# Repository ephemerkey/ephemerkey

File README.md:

# ephemerkey

A battery-powered, **GPS-geofenced TOTP code generator**. It produces RFC 6238
time-based one-time passwords (TOTP) — but only when the device holds a valid
GNSS fix inside an authorized geofence. Outside the fence, no codes. A companion
analog "TOTP lock" board consumes the codes and drives an actuator.

> Time comes from GNSS (disciplined RTC), place comes from GNSS — so a code is
> proof of *being in the right place at the right time*.

## Features

- **GNSS time + place**: u-blox MAX-M10S provides UTC time (TIMEPULSE-disciplined
  RTC) and a position fix. Codes are gated on both an accurate clock and a fix
  inside the configured geofence.
- **RFC 6238 TOTP**: SHA1/HMAC/Base32 engine from the `smalltotp` library,
  6-digit / 30-second codes (configurable).
- **Ultra-low-power**: STM32U083 (Cortex-M0+ ULP) + TPS63900 buck-boost with
  nanoamp-class quiescent current for long battery life; GNSS duty-cycled.
- **Tamper / motion**: LIS3DH accelerometer for wake-on-motion and tamper
  detection (optionally zeroizes the secret on tamper).
- **Single coin/Li-ion cell** input via buck-boost (works above and below 3.3 V).

## Architecture

```
                    ┌───────────────── RF ─────────────────┐
   W3011A chip ANT ─┤  (50Ω + π-match)                      │
                    └──────────────┬───────────────────────┘
                                   │ RF_IN
                          ┌────────┴─────────┐
                          │  MAX-M10S-00B    │  u-blox M10 GNSS
                          │  (TCXO, LNA, SAW)│
                          └─┬───┬────┬───┬───┘
                   UART(TXD/RXD)│    │TIMEPULSE (1 PPS → RTC discipline)
                            │   │EXTINT (wake)
                            │   │
   batt ── TPS63900 ──3V3───┼───┴──────────────┐
   (buck-boost,             │                  │
    ultra-low Iq)           │ USART1           │ V_BCKP (RTC/GNSS backup)
                     ┌───────┴────────┐         │
                     │  STM32U083KCU6 │         │
                     │  Cortex-M0+    │── RTC ──┘ (TOTP time base)
                     │  256KB flash   │
                     └─┬────┬────┬────┘
                  I2C  │    │    │ SWD (PA13/PA14)
                  ┌────┴──┐ │    │
                  │LIS3DH │ │    └── USB (PA11/PA12) — provisioning/console
                  │ accel │ │
                  └───────┘ └── code out → companion "TOTP lock" board
                  (motion/tamper)   (UART / open-drain / display)
```

## Repository Structure

```
ephemerkey/
├── hardware/                    # PCB design (KiCad 10, CERN-OHL-P v2)
│   ├── lib/                     # empty — anchor parts use KiCad bundled libs
│   │   ├── symbols/             #   (reserved for future custom symbols)
│   │   ├── footprints.pretty/   #   (reserved for future custom footprints)
│   │   └── 3dmodels/            #   (reserved for future 3D STEP models)
│   ├── ephemerkey/              # The generator board
│   │   ├── ephemerkey.kicad_pro
│   │   ├── ephemerkey.kicad_sch # Top-level: MCU, USB, SWD, button, LED
│   │   ├── psu.kicad_sch        # Battery → TPS63900 buck-boost sub-sheet
│   │   ├── gnss.kicad_sch       # MAX-M10S + W3011A antenna sub-sheet
│   │   └── sensors.kicad_sch    # LIS3DH accelerometer sub-sheet
│   ├── scripts/
│   ├── Makefile
│   ├── sym-lib-table
│   └── fp-lib-table
├── firmware/
│   ├── ephemerkey-stm32/        # STM32U083 application (STM32CubeU0 HAL)
│   ├── common/                  # Shared HAL/utilities
│   ├── shared/                  # Shared protocol definitions
│   └── LICENSE                  # Apache 2.0
├── reference/                   # Datasheets, source-skeleton pointers
├── DESIGN.md                    # Full hardware/firmware design document
└── LICENSE
```

## Key Components

| Component | Part | Package | Purpose |
|-----------|------|---------|---------|
| MCU | STM32U083KCU6 | UFQFPN-32 | ULP Cortex-M0+, 256KB flash, RTC, USB, TOTP engine |
| GNSS | MAX-M10S-00B | LGA (9.7×10mm) | u-blox M10: UTC time + position fix |
| GPS antenna | W3011A | SMD chip | 1.559–1.606 GHz GNSS antenna |
| Power | TPS63900DSKR | VSON-10 | Buck-boost, nanoamp Iq, single-cell → 3V3 |
| Accelerometer | LIS3DHTR | LGA-16 | Motion wake + tamper detection |

## Companion Project

The **TOTP lock** (separate analog board) reads the code stream from this
generator and drives an actuator (solenoid/relay). ephemerkey is the *generator*
half; the lock is the *consumer* half. The interface is documented in
`DESIGN.md` (§ Code Output Interface).

## License

- **Hardware**: CERN-OHL-P v2 (permissive open hardware)
- **Firmware**: Apache 2.0 (TOTP engine via smalltotp, also Apache 2.0)

Copyright (c) 2025-2026 EphemerKey Authors

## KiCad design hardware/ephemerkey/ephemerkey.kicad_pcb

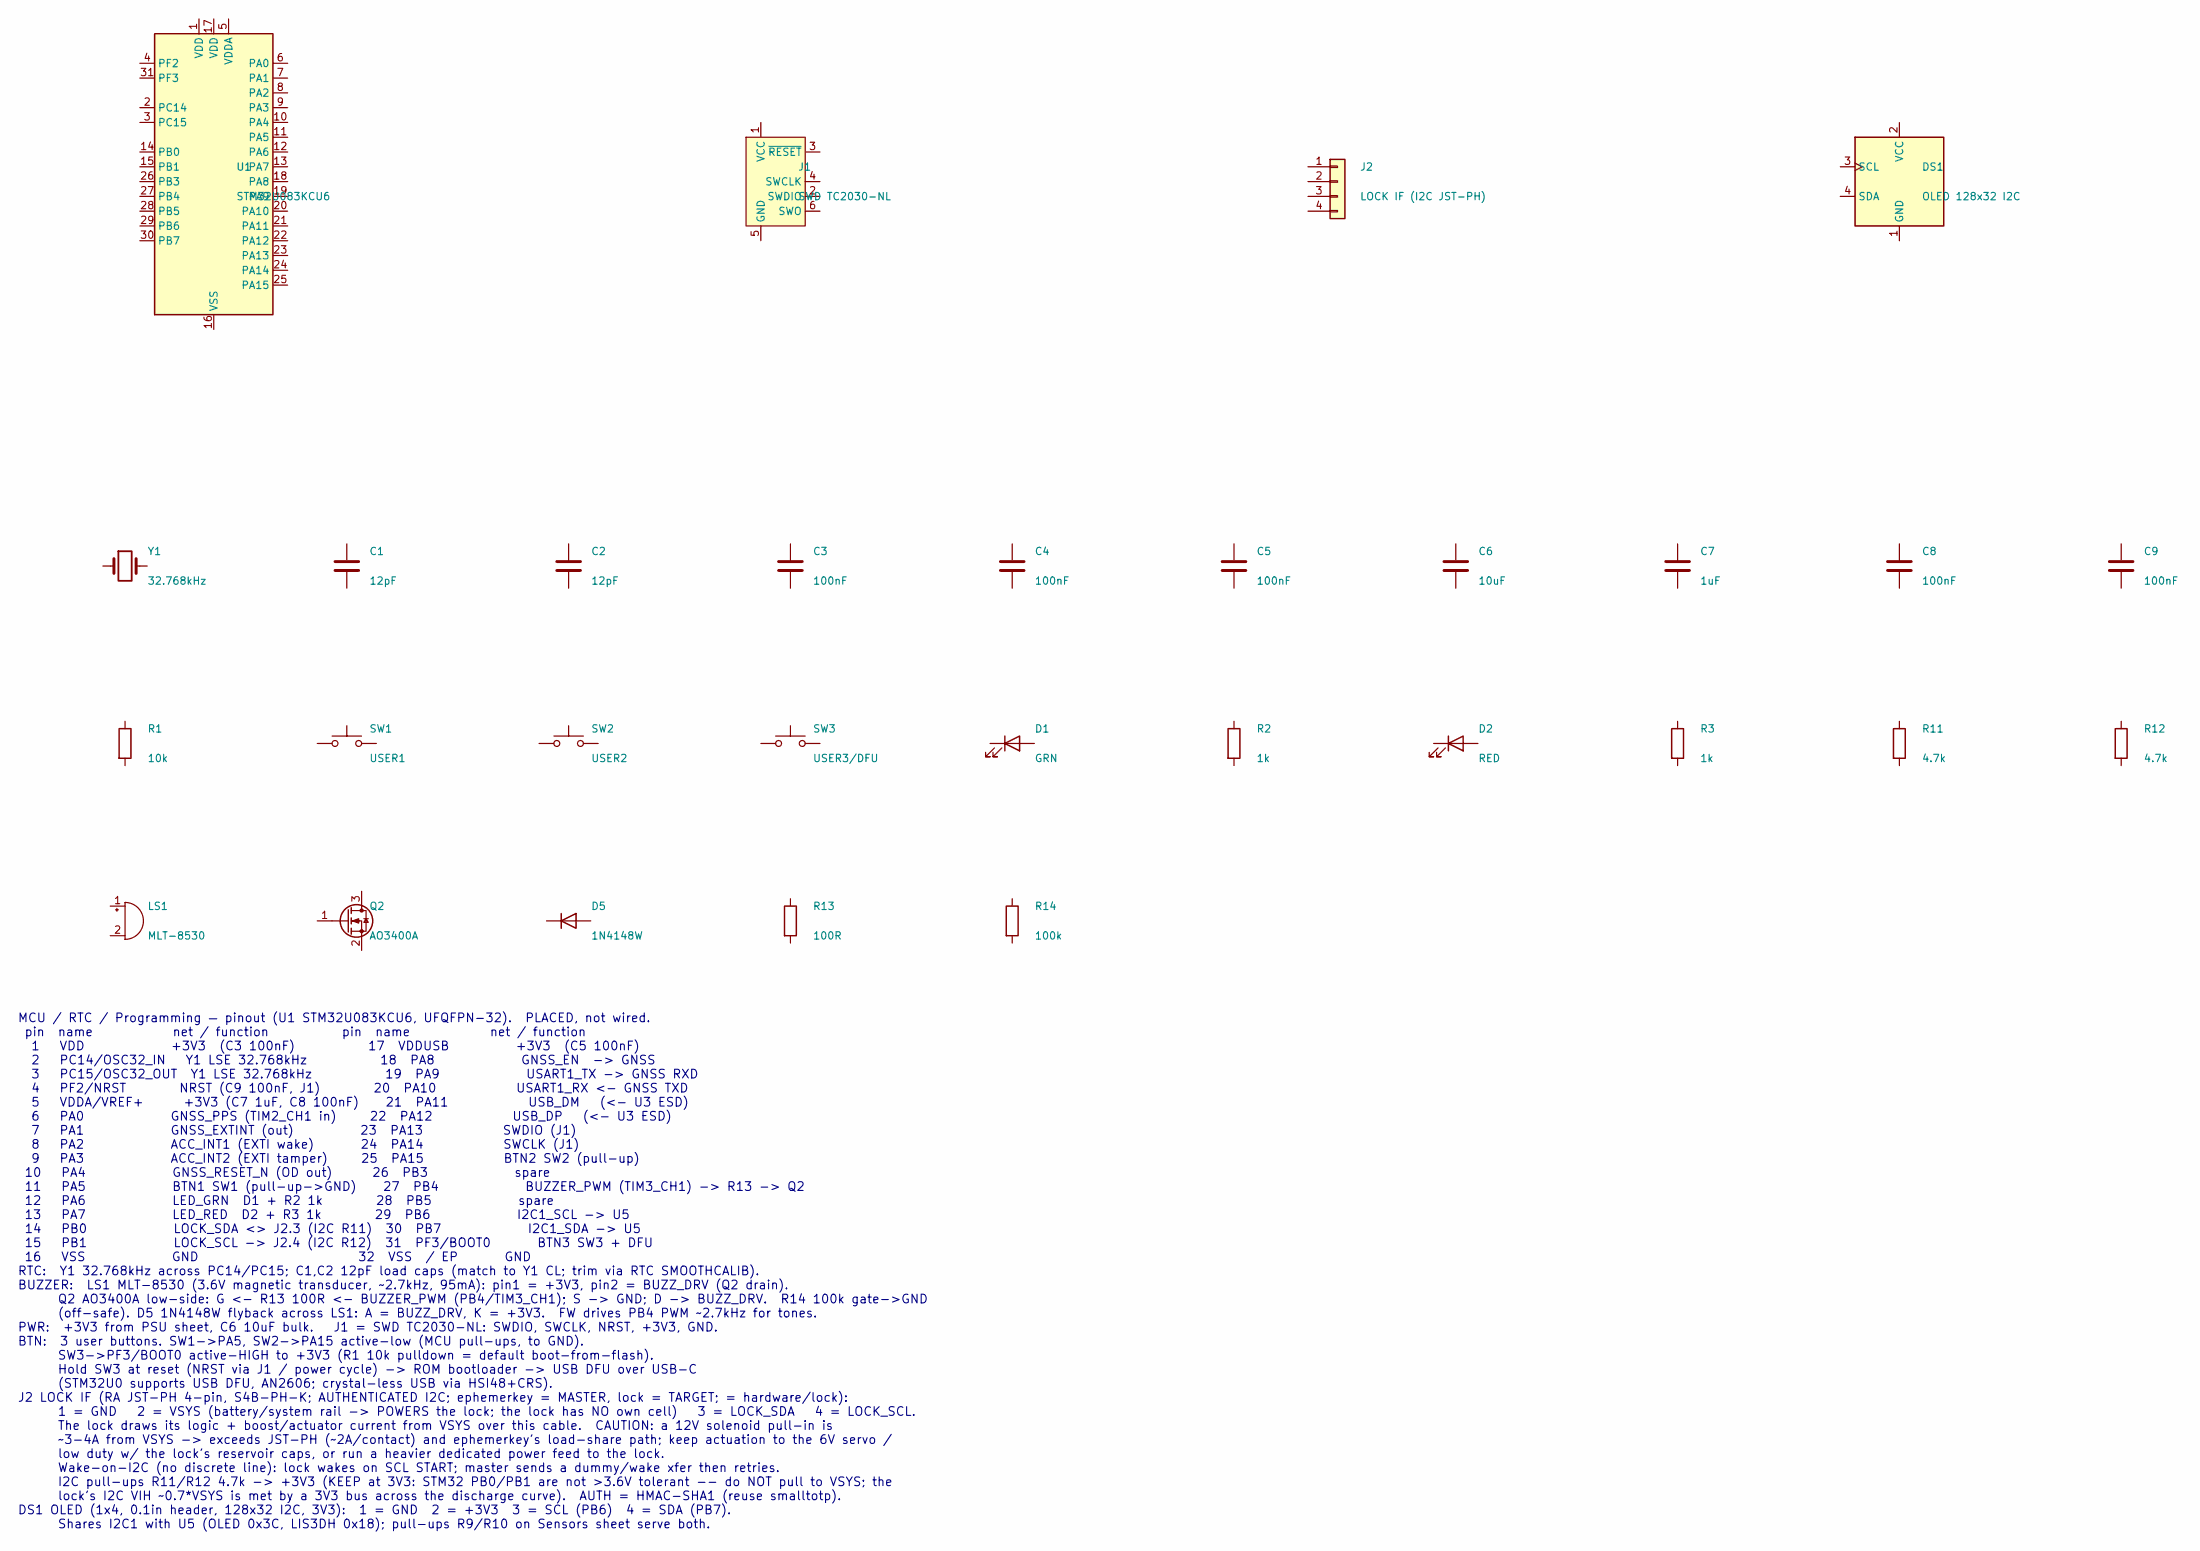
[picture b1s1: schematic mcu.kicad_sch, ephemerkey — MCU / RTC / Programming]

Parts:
C1, C2: 12pF; C_0402_1005Metric; LCSC C1547
C3, C4, C5, C8, C9: 100nF; C_0402_1005Metric; LCSC C1525
C6: 10uF; C_0805_2012Metric; LCSC C15850
C7: 1uF; C_0402_1005Metric; LCSC C29266
D1: GRN; LED_0402_1005Metric; MPN LTST-C281KGKT; LCSC C160479
D2: RED; LED_0402_1005Metric; MPN NCD0402R1; LCSC C130719
D5: 1N4148W; D_SOD-123; MPN 1N4148W; LCSC C81598
DS1: OLED 128x32 I2C; PinSocket_1x04_P2.54mm_Vertical
J1: SWD TC2030-NL; Tag-Connect_TC2030-IDC-NL_2x03_P1.27mm_Vertical
J2: LOCK IF (I2C JST-PH); JST_PH_S4B-PH-K_1x04_P2.00mm_Horizontal; MPN S4B-PH-K-S; LCSC C157926
LS1: MLT-8530; MagneticBuzzer_CUI_CMT-8504-100-SMT; MPN MLT-8530; LCSC C94599
Q2: AO3400A; SOT-23; MPN AO3400A; LCSC C20917
R1: 10k; R_0402_1005Metric; LCSC C25744
R2, R3: 1k; R_0402_1005Metric; LCSC C11702
R11, R12: 4.7k; R_0402_1005Metric; LCSC C25900
R13: 100R; R_0402_1005Metric; LCSC C106232
R14: 100k; R_0402_1005Metric; LCSC C25741
SW1: USER1; SW_Push_1P1T_XKB_TS-1187A; MPN TS-1187A-B-A-B; LCSC C318884
SW2: USER2; SW_Push_1P1T_XKB_TS-1187A; MPN TS-1187A-B-A-B; LCSC C318884
SW3: USER3/DFU; SW_Push_1P1T_XKB_TS-1187A; MPN TS-1187A-B-A-B; LCSC C318884
U1: STM32U083KCU6; UFQFPN-32-1EP_5x5mm_P0.5mm_EP3.5x3.5mm; MPN STM32U083KCU6; LCSC C22459164
Y1: 32.768kHz; Crystal_SMD_3215-2Pin_3.2x1.5mm; MPN Q13FC13500004; LCSC C32346

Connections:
unnamed: U1.16 (VSS), U1.32 (VSS), U1.33 (VSS)

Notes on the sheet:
MCU / RTC / Programming — pinout (U1 STM32U083KCU6, UFQFPN-32). PLACED, not wired. pin name net / function pin name net / function 1 VDD +3V3 (C3 100nF) 17 VDDUSB +3V3 (C5 100nF) 2 PC14/OSC32_IN Y1 LSE 32.768kHz 18 PA8 GNSS_EN -> GNSS 3 PC15/OSC32_OUT Y1 LSE 32.768kHz 19 PA9 USART1_TX -> GNSS RXD 4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

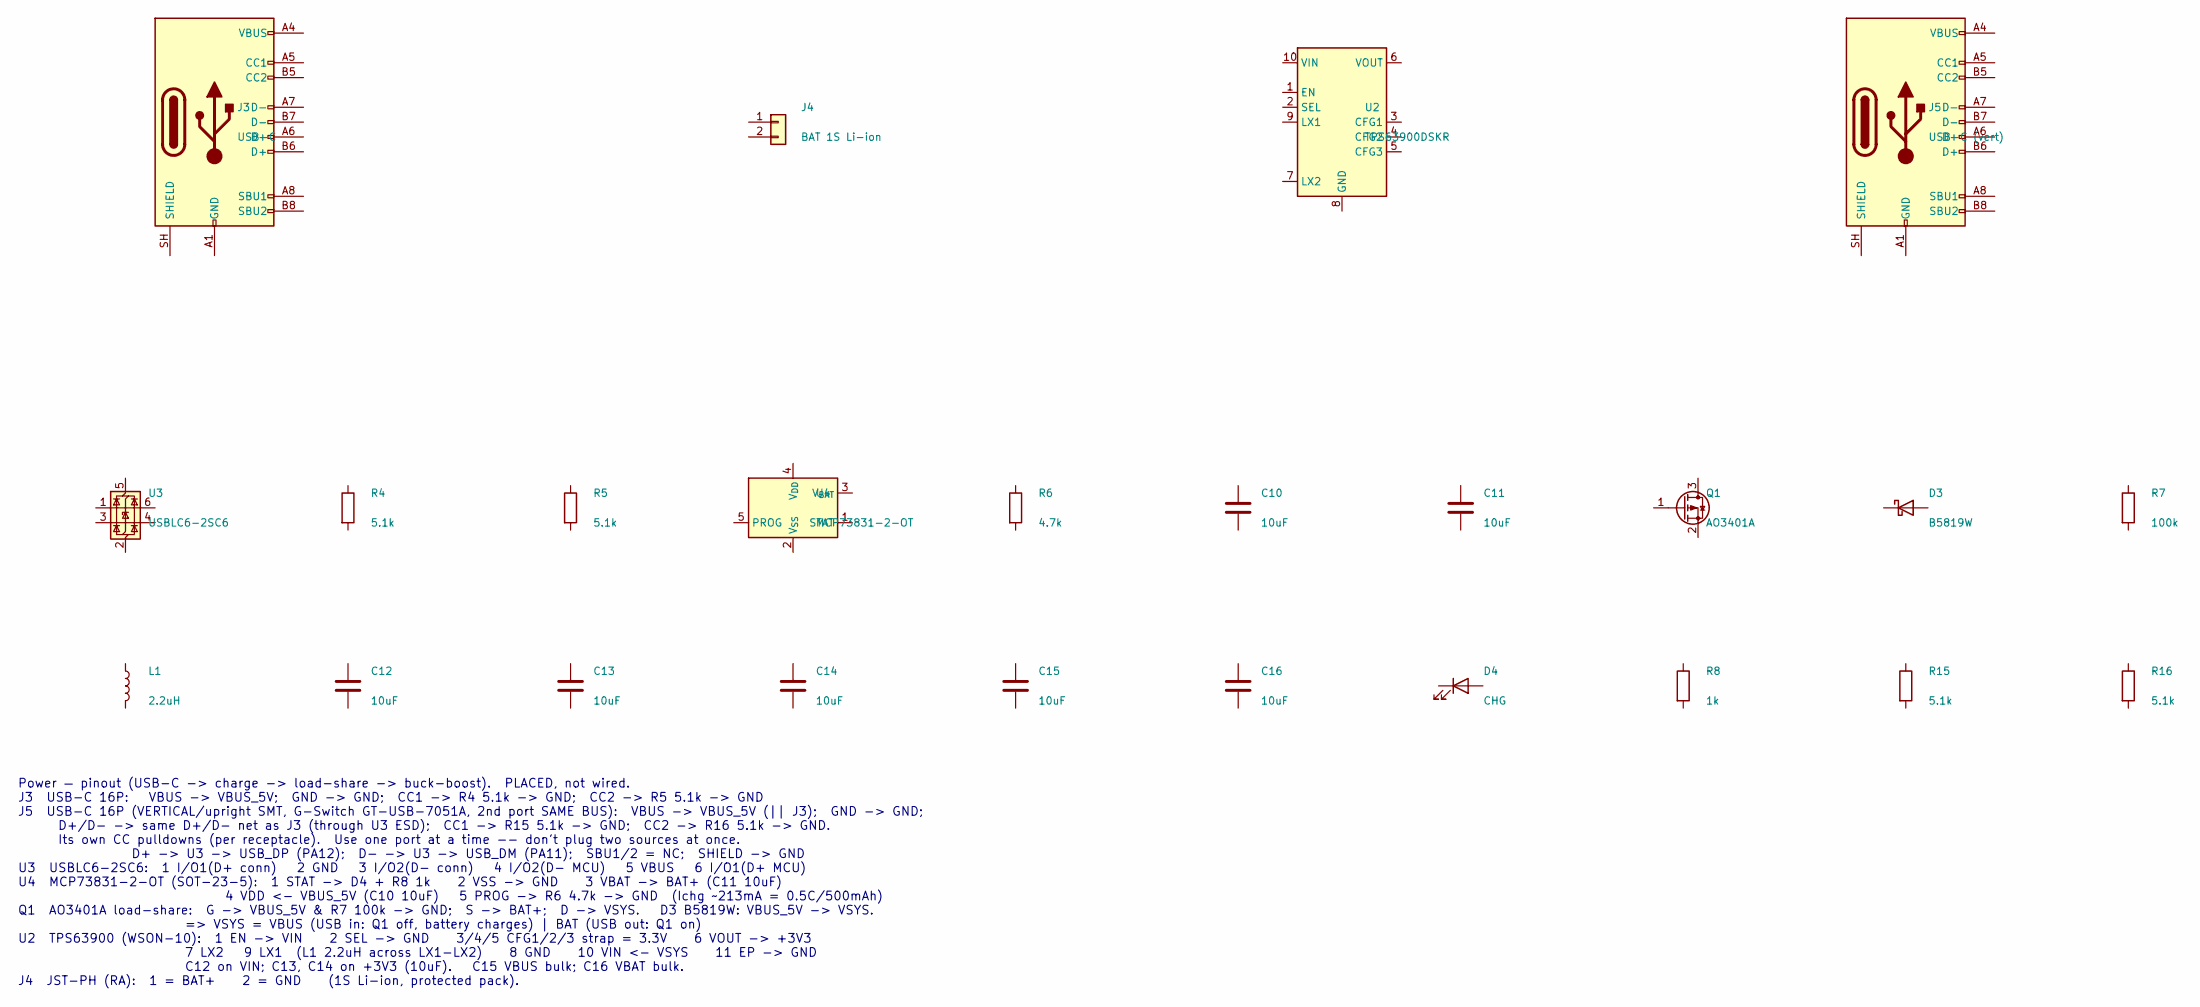
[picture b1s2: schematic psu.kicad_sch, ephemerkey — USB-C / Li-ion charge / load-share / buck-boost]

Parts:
C10, C11, C12, C13, C14, C15, C16: 10uF; C_0805_2012Metric; LCSC C15850
D3: B5819W; D_SOD-123; MPN B5819W; LCSC C8598
D4: CHG; LED_0402_1005Metric; MPN NCD0402R1; LCSC C130719
J3: USB-C; USB_C_Receptacle_GCT_USB4105-xx-A_16P_TopMnt_Horizontal; MPN USB-TYPE-C-019; LCSC C2927039
J4: BAT 1S Li-ion; JST_PH_S2B-PH-K_1x02_P2.00mm_Horizontal; MPN S2B-PH-K-S; LCSC C173752
J5: USB-C (vert); USB_C_Receptacle_G-Switch_GT-USB-7051x; MPN GT-USB-7051A; LCSC C2843970
L1: 2.2uH; L_Changjiang_FNR3015S; MPN FNR3015S2R2MT; LCSC C167747
Q1: AO3401A; SOT-23; MPN AO3401A; LCSC C15127
R4, R5, R15, R16: 5.1k; R_0402_1005Metric; LCSC C25905
R6: 4.7k; R_0402_1005Metric; LCSC C25900
R7: 100k; R_0402_1005Metric; LCSC C25741
R8: 1k; R_0402_1005Metric; LCSC C11702
U2: TPS63900DSKR; WSON-10-1EP_2.5x2.5mm_P0.5mm_EP1.2x2mm; MPN TPS63900DSKR; LCSC C1518762
U3: USBLC6-2SC6; SOT-23-6; MPN USBLC6-2SC6; LCSC C2687116
U4: MCP73831-2-OT; SOT-23-5; MPN MCP73831T-2ACI/OT; LCSC C424093

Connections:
unnamed: J3.A1 (GND), J3.A12 (GND), J3.B1 (GND), J3.B12 (GND)
unnamed: J3.A4 (VBUS), J3.A9 (VBUS), J3.B4 (VBUS), J3.B9 (VBUS)
unnamed: J5.A1 (GND), J5.A12 (GND), J5.B1 (GND), J5.B12 (GND)
unnamed: J5.A4 (VBUS), J5.A9 (VBUS), J5.B4 (VBUS), J5.B9 (VBUS)
unnamed: U2.8 (GND), U2.11 (GND)

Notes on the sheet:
Power — pinout (USB-C -> charge -> load-share -> buck-boost). PLACED, not wired. J3 USB-C 16P: VBUS -> VBUS_5V; GND -> GND; CC1 -> R4 5.1k -> GND; CC2 -> R5 5.1k -> GND J5 USB-C 16P (VERTICAL/upright SMT, G-Switch GT-USB-7051A, 2nd port SAME BUS): VBUS -> VBUS_5V (|| J3); GND -> GND; D+/D- -> same 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

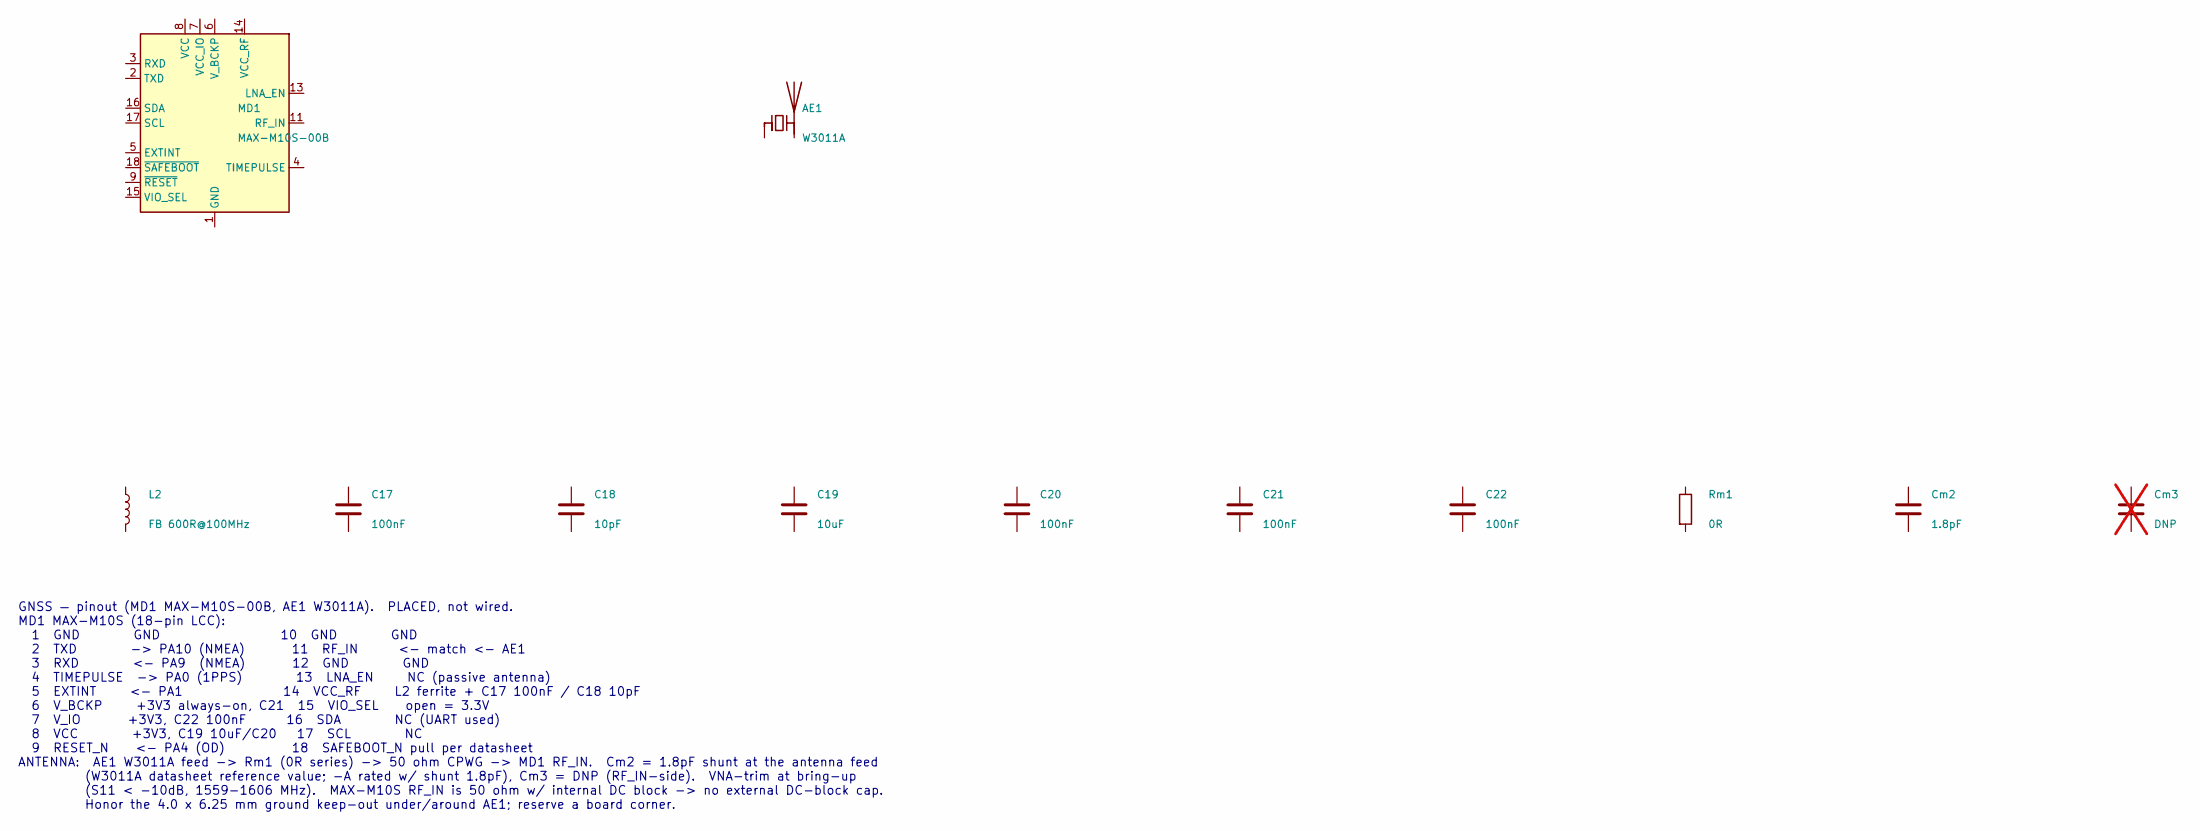
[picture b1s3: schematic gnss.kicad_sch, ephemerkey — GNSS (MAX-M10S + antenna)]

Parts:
AE1: W3011A; Pulse_W3011; MPN W3011A; LCSC C5830926
C17, C20, C21, C22: 100nF; C_0402_1005Metric; LCSC C1525
C18: 10pF; C_0402_1005Metric
C19: 10uF; C_0805_2012Metric; LCSC C15850
Cm2: 1.8pF; C_0402_1005Metric; LCSC C1549
Cm3: DNP; C_0402_1005Metric; not fitted
L2: FB 600R@100MHz; L_0402_1005Metric; MPN BLM15AG601SN1D; LCSC C76884
MD1: MAX-M10S-00B; ublox_MAX; MPN MAX-M10S-00B; LCSC C4153167
Rm1: 0R; R_0402_1005Metric; LCSC C17168

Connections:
unnamed: MD1.1 (GND), MD1.10 (GND), MD1.12 (GND)

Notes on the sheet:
GNSS — pinout (MD1 MAX-M10S-00B, AE1 W3011A). PLACED, not wired. MD1 MAX-M10S (18-pin LCC): 1 GND GND 10 GND GND 2 TXD -> PA10 (NMEA) 11 RF_IN <- match <- AE1 3 RXD <- PA9 (NMEA) 12 GND GND 4 TIMEPULSE -> PA0 (1PPS) 13 LNA_EN NC (passive antenna) 5 EXTINT <- PA1 14 VCC_RF L2 ferrite + C17 100nF / C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

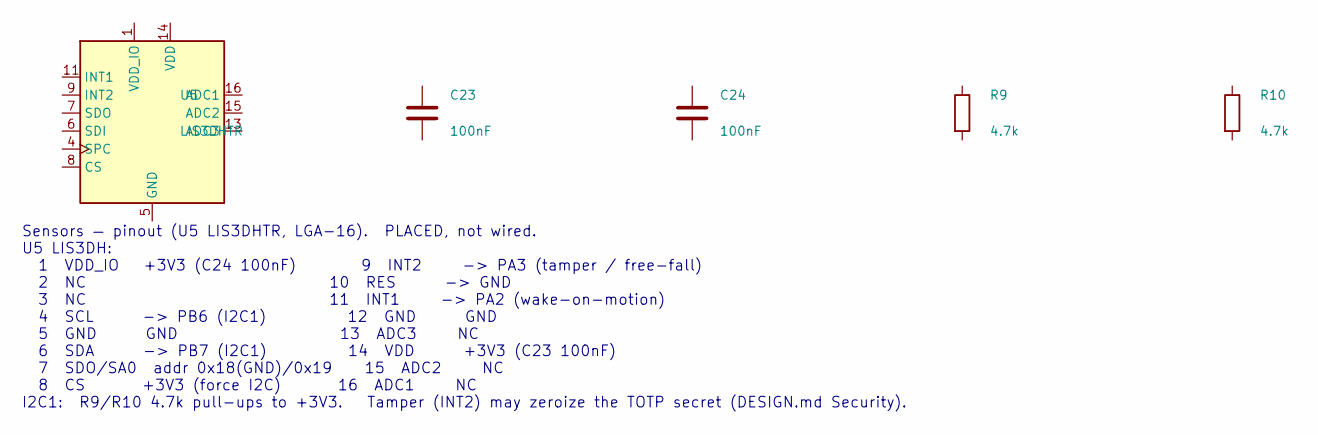
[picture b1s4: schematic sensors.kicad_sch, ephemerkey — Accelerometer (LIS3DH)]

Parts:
C23, C24: 100nF; C_0402_1005Metric; LCSC C1525
R9, R10: 4.7k; R_0402_1005Metric; LCSC C25900
U5: LIS3DHTR; LGA-16_3x3mm_P0.5mm; MPN LIS3DHTR; LCSC C15134

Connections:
unnamed: U5.5 (GND), U5.10 (GND), U5.12 (GND)

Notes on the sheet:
Sensors — pinout (U5 LIS3DHTR, LGA-16). PLACED, not wired. U5 LIS3DH: 1 VDD_IO +3V3 (C24 100nF) 9 INT2 -> PA3 (tamper / free-fall) 2 NC 10 RES -> GND 3 NC 11 INT1 -> PA2 (wake-on-motion) 4 SCL -> PB6 (I2C1) 12 GND GND 5 GND GND 13 ADC3 NC 6 SDA -> PB7 (I2C1) 14 VDD +3V3 (C23 100nF) 7 SDO/SA0 addr 0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

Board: 2 copper layers, 70 parts (0 on the bottom side), 8 nets, no tracks yet.

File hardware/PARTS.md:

# ephemerkey — Parts (BOM source of truth)

Every line resolves to a real KiCad **bundled** symbol + footprint and a JLCPCB
**LCSC** number. 0402 passives throughout; bulk caps 0805. Charge current set for
a ~500 mAh 1S Li-ion (Rprog 4.7 kΩ ≈ 213 mA, ~0.5 C). The schematic is generated
from `scripts/ephemerkey.schgen.py` — **edit that, not the `.kicad_sch` files**.

> JLCPCB Basic vs Extended: the jlcsearch API under-reports the Basic flag, so
> verify in JLCPCB's BOM tool at order time. The common 0402 R/C (Uniohm/Samsung)
> and SOT-23 jellybeans here are Basic; the ICs, crystal, inductor, connectors,
> and LEDs are Extended.

## Actives / modules

| Ref | Value | MPN | LCSC | Footprint |
|-----|-------|-----|------|-----------|
| U1 | STM32U083KCU6 | STM32U083KCU6 | C22459164 | ephemerkey:UFQFPN-32-1EP_5x5mm_P0.5mm_EP3.5x3.5mm (project copy → generic QFN-32 3D model) |
| MD1 | MAX-M10S-00B | MAX-M10S-00B | C4153167 | ephemerkey:ublox_MAX (project copy + vendored 3D model) |
| AE1 | W3011A | W3011A | C5830926 | RF_Antenna:Pulse_W3011 |
| U2 | TPS63900DSKR | TPS63900DSKR | C1518762 | Package_SON:WSON-10-1EP_2.5x2.5mm_P0.5mm_EP1.2x2mm |
| U3 | USBLC6-2SC6 | USBLC6-2SC6 | C2687116 | Package_TO_SOT_SMD:SOT-23-6 |
| U4 | MCP73831-2-OT | MCP73831T-2ACI/OT | C424093 | Package_TO_SOT_SMD:SOT-23-5 |
| U5 | LIS3DHTR | LIS3DHTR | C15134 | Package_LGA:LGA-16_3x3mm_P0.5mm |
| Q1 | AO3401A (P-FET) | AO3401A | C15127 | Package_TO_SOT_SMD:SOT-23 |
| D3 | B5819W (Schottky) | B5819W | C8598 | Diode_SMD:D_SOD-123 |

## Frequency / power magnetics

| Ref | Value | MPN | LCSC | Footprint | Note |
|-----|-------|-----|------|-----------|------|
| Y1 | 32.768 kHz | Q13FC13500004 | C32346 | Crystal:Crystal_SMD_3215-2Pin_3.2x1.5mm | RTC LSE; match load caps to CL |
| L1 | 2.2 µH | FNR3015S2R2MT | C167747 | Inductor_SMD:L_Changjiang_FNR3015S | TPS63900 (3×3 mm, small) |
| L2 | FB 600Ω@100MHz | BLM15AG601SN1D | C76884 | Inductor_SMD:L_0402_1005Metric | VCC_RF isolation |

## Connectors / switch / LEDs

| Ref | Value | MPN | LCSC | Footprint |
|-----|-------|-----|------|-----------|
| J3 | USB-C (GCT USB4105) | USB-TYPE-C-019 | C2927039 | Connector_USB:USB_C_Receptacle_GCT_USB4105-xx-A_16P_TopMnt_Horizontal |
| J4 | BAT 1S (JST PH RA) | S2B-PH-K-S | C173752 | Connector_JST:JST_PH_S2B-PH-K_1x02_P2.00mm_Horizontal |
| J1 | SWD | Conn_ARM_SWD_TagConnect_TC2030-NL | — | Connector:Tag-Connect_TC2030-IDC-NL_2x03_P1.27mm_Vertical |
| J2 | LOCK OUT (1x4) | header 2.54 | — | Connector_PinHeader_2.54mm:PinHeader_1x04_P2.54mm_Vertical |
| DS1 | OLED 128x32 I2C (1x4, 0.1") | `Display_Graphic:ER_OLEDM0.91_1x-I2C` | — | 1x4 female socket P2.54 (PinSocket_1x04): GND/VCC/SCL/SDA → I2C1 |
| SW1–SW3 | USER1/2/3 (SW3=BOOT0/DFU) | TS-1187A-B-A-B | C318884 | ephemerkey:SW_Push_1P1T_XKB_TS-1187A (vendored from tsumikoro, has 3D model) |
| D1 | LED green (status) | LTST-C281KGKT | C160479 | LED_SMD:LED_0402_1005Metric |
| D2 / D4 | LED red (fault / charge) | NCD0402R1 | C130719 | LED_SMD:LED_0402_1005Metric |

## 0402 passives (Basic)

| Value | LCSC | Used for |
|-------|------|----------|
| R 5.1k | C25905 | USB-C CC1/CC2 (R4,R5) |
| R 4.7k | C25900 | Rprog (R6, 213 mA), I²C pull-ups (R9,R10) |
| R 100k | C25741 | load-share gate pulldown (R7) |
| R 10k | C25744 | BOOT0 pulldown (R1) |
| R 1k | C11702 | LED series (R2,R3,R8) |
| R 0Ω | C17168 | antenna π-match series (Rm1) |
| C 100nF | C1525 | decoupling (C3,C4,C5,C8,C9,C17,C20,C21,C22,C23,C24) |
| C 1µF | C29266 | VDDA/VREF+ filter (C7) |
| C 12pF | C1547 | LSE load caps (C1,C2) — tune to crystal CL |
| C 10pF | (TBD) | VCC_RF HF bypass (C18) |
| C 10µF 0805 | C15850 | bulk: 3V3, charger, buck-boost, VBUS/VBAT, GNSS VCC (C6,C10–C16,C19) |
| C DNP | — | antenna π-match shunts (Cm2,Cm3 — fit at bring-up) |

## Notes
- **Rprog → charge current:** I_chg ≈ 1000 V / Rprog. 4.7 kΩ = 213 mA (~0.5 C of
  500 mAh). Use 3.9 kΩ for ~256 mA if faster charging is wanted.
- **LSE load caps:** 12 pF shown; set to ≈2·(CL − C_stray) for the chosen Y1 CL,
  trim residual with the STM32 RTC SMOOTHCALIB.
- **3 parts need a downloaded 3D model** (STM32U083KCU6, MAX-M10S, W3011A) — see
  `lib/3dmodels/README.md`.

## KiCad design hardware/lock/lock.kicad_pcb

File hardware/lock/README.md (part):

# lock — companion TOTP lock board

The **consumer** half of the ephemerkey system, and the **second PCB in this
repo** (alongside `hardware/ephemerkey/`, sharing the same `scripts/kschgen.py`
engine, `Makefile`, and lib tables — the multi-project layout used by
`reefvolt-sensorbuddy`). ephemerkey *generates* an authenticated unlock; this
board *verifies* it and drives the actuator.

```
make gen-lock      # regenerate the schematic from scripts/lock.schgen.py (placed, not wired)
make check-lock    # component/footprint/dup-ref/ERC tally
make render-lock   # per-sheet PNGs
```

The schematic is **generated from a manifest** (`scripts/lock.schgen.py`), like
ephemerkey. Components are **placed, not wired** — each sheet carries an
on-canvas note that is the wiring spec for the eeschema phase. Regenerate
*before* wiring (regen reassigns UUIDs).

## What it does

1. Sleeps at ~0.1 µA (ATtiny1616 power-down). Coil de-energized, 12 V rail off.
2. ephemerkey starts an I2C transaction; the first START wakes the MCU (wake-on-I2C).
3. **Authenticated** challenge-response over I2C proves the request is
   genuine (HMAC-SHA1, shared secret in flash — see *Firmware plan*).
4. On success: enable the boost, run the **peak-and-hold** solenoid profile,
   then drop the rail and go back to sleep.

Everything (MCU + boost + driver) is **powered from ephemerkey over the I2C
connector** (J2.2 = VSYS, ephemerkey's ~3.0–4.7 V battery/system rail). The lock
carries **no local battery** (J1 removed). See the *current caveat* under the
interface section — a 12 V solenoid pull-in draws several amps through that cable.

## Architecture

```
 VSYS from ephemerkey ──┬─────────────────────────────► U1 ATtiny1616 VCC   (direct, NO LDO; ~0.1µA sleep)
   (J2.2, I2C connector) │                            │  PA5 SOL_PWM ─┐   PB0/PB1 I2C ── J2 (target; key=master)
                           │                            │  PA6 SOL_BOOST_EN  wake-on-I2C: SCL START (no wake line)
                           │   SOL_BOOST_EN ──► EN       │  PA0 UPDI ─────── J4 (program)
                           └─► U2 MT3608 boost ──► +12V (VSOL) ─┬─ C5 220µF + C6 22µF  (reservoir)
                               L1 10µH · D2 SS34               │
                               FB: R3 200k / R4 10k ≈ 12.6V    ▼
                                                          ┌─ SOLENOID ─┐  (J3 JST-PH)
                                                  D3 SS34 │            │
                                                  flyback └─────┬──────┘
                                                                │ SOL_DRV (drain)
                                                  SOL_PWM ─[R5 100R]─┤ Q1 AO3400A (low-side)
                                                              [R6 100k]│
                                                                    GND┘
```

Sheets: **MCU** (`mcu.kicad_sch`) · **PWR** (`psu.kicad_sch`) · **DRV** (`drv.kicad_sch`).

## BOM (all JLCPCB / LCSC)

| Ref | Part | Value | LCSC | JLC | Footprint |
|-----|------|-------|------|-----|-----------|
| U1 | ATtiny1616 | tinyAVR-1, runs 1.8–5.5 V | C507118 | ext | QFN-20 3×3 0.4 mm |
| U2 | MT3608 | boost, ~2 A switch | C84817 | ext | SOT-23-6 |
| Q1,Q2,Q4,Q5 | AO3400A | N-FET (solenoid LS, FB switch, servo logic, interlock) | C20917 | **Basic** | SOT-23 |
| Q3 | AO3401A | P-FET (servo high-side load switch) | C15127 | **Basic** | SOT-23 |
| D2,D3 | SS34 | Schottky 40 V/3 A | C8678 | **Basic** | SMA |
| L1 | FNR6045S100MT | 10 µH power inductor | C168076 | ext | 6×6 mm |
| C5,C8 | 220 µF 25 V | reservoir / VSERVO bulk (electrolytic) | C4747974 | ext | Ø6.3×7.7 |
| C4,C6 | 22 µF 25 V | boost out / VSOL bypass | C12891 | **Basic** | 1206 |
| C3 | 10 µF 25 V | boost in | C15850 | **Basic** | 0805 |
| C1,C2,C7,C9,C10 | 100 nF / 1 µF / 1 nF | decouple / hall debounce / snubber(DNP) | C1525/C29266 | **Basic** | 0402 |
| R3 | 200 k | FB top | C25764 | **Basic** | 0402 |
| R4 | 22 k | FB base → 6 V default | C25768 | **Basic** | 0402 |
| R17 | 20 k | FB switch → 12 V (Q2) | C25765 | **Basic** | 0402 |
| R2,R6,R18,R19,R20 | 100 k | pulldowns / P-FET gate pull-up | C25741 | **Basic** | 0402 |
| R16,R21,R22,R23,R25 | 10 k | servo pulldowns/series, hall pull-ups | C25744 | **Basic** | 0402 |
| R5 | 100 Ω | gate series | C106232 | ext* | 0402 |
| R1,R15,R24 | 1 k | status LED / servo signal series | C11702 | **Basic** | 0402 |
| D1 | LED green | status (driven by **PC3**) | C160479 | ext | 0402 |
| J3 | JST-PH 2-pin | solenoid | C173752 | ext | PH 2.0 |
| J2 | JST-PH 4-pin RA (S4B-PH-K) | I2C link (right-angle) | C157926 | ext | PH 2.0 RA |
| J4 | pin header 1×3 | UPDI program | — | — | 1×3 |
| J5,J8 | pin header 1×3 | servo outputs (S/V+/GND), DNP unless servo build | — | — | 1×3 |
| R13,R14 | 0 Ω | VSERVO source select (fit one) | C17168 | **Basic** | 0402 |
| J6,J7 | JST-PH 3-pin RA (S3B-PH-K) | door / bolt hall sensors | C157929 | ext | PH 2.0 RA |

\* jlcsearch under-reports Basic flags; verify in JLCPCB's BOM tool at order time.

Every footprint is a KiCad-bundled package, so **all parts carry 3D models** — the
board is clearance-checkable in KiCad's 3D viewer once it's laid out.

## Boost + reservoir sizing (read before ordering)

12 V × up to 1 A ≈ **12 W ≈ ~3.8 A from the cell** — heavy. The design splits it:

- The **MT3608** is sized for the **hold** current (~0.3 A @ 12 V ≈ within its
  ~0.5 A @ 12 V capability) plus recharging the reservoir between actuations.
- The **reservoir** (C5) supplies the brief **pull-in** surge. Sizing:
  `ΔV ≈ I_pull · t_pull / C`. A 1 A, 30 ms pull-in pulls 30 mC; with 220 µF that
  sags the rail a lot, so **220 µF is the baseline for ≤ ~500 mA / short
  pull-ins**. For a true sustained **1 A @ 12 V pull-in**, either grow C5 into
  the multi-thousand-µF range **or** swap the MT3608 for a **TPS61088-class**
  boost that can source the full 12 W directly. Pin this down against the actual
  solenoid's pull-in current × time and re-fire rate.

Set Vout exactly with the FB divider: `Vout = 0.6·(1 + R3/R4)`. 200 k/10 k ≈
12.6 V; trim R3 toward 12.0 V if desired.

## Servo variant + firmware actuator control

The board drives a **12 V solenoid** or a **6 V RC servo**. Because the boost
voltage and the servo power are both firmware-controlled, **one fully-populated board
can carry both** and switch between them (one actuator active at a time — a single
boost = a single voltage). Firmware drives three lines:

- **`BOOST_VSEL`** (PA1) — picks the rail: low/default **6 V** (servo-safe), high
  **12 V** (solenoid). NMOS Q2 switches R17 across the FB divider.
- **`SERVO_PWR_EN`** (PA2) — high-side P-FET (Q3) load switch on VSERVO. Servo power
  comes on only when firmware asserts it **and** the boost is at 6 V: a **hardware
  interlock** (Q5, gated by `BOOST_VSEL`) forces servo power OFF at 12 V regardless of
  firmware, so a 12 V solenoid pulse can never reach a 6 V servo.
- **`SERVO_SIG`** (PB2 / TCA0) — 50 Hz position pulse, via R15 (1 k) + R16 (10 k idle
  pulldown) so the servo can't twitch at boot.

| Mode | BOOST_VSEL | SERVO_PWR_EN | Actuator |
|------|-----------|--------------|----------|
| Solenoid | 12 V | off (interlock-forced) | Q1/D3/J3 peak-and-hold |
| Servo, 6 V | 6 V | on | J5 servo, VSERVO ← VSOL (`R13`, populated) |
| Servo, direct | boost off | on | J5 servo, VSERVO ← VSYS (`R14`, DNP alt) |

- **J5 / J8** — two 3-pin RC-servo outputs (`1=SIG, 2=V+ (VSERVO), 3=GND`), e.g. a
  dual-latch lock. `SERVO_SIG` (PB2/TCA0) and `SERVO_SIG2` (PB4, software-timed);
  both share the `VSERVO` rail and the load-switch/interlock. MT3608 ~1 A @ 6 V —
  drive them sequentially, or upsize C5/C8 for simultaneous travel.
- **VSERVO source** — fit **exactly one** 0 Ω: `R13 = VSOL` (6 V from the boost —
  the populated default) or `R14 = VSYS` (servo direct off the connector rail,
  ~3–4.7 V). **Never both.** C8 (220 µF) buffers servo inrush.
- `SERVO_SIG` is VSYS-level logic (~3–4.7 V), accepted by typical servos, GND-referenced.

## Authenticated digital interface + Firmware plan

The ephemerkey↔lock link is an authenticated I2C bus — **ephemerkey is the
master**, this lock is the target — on a **right-angle 4-pin JST-PH** (`S4B-PH-K`,
a standard 4-pin I2C cable, straight-through):

| Pin | lock (this board, target) | ephemerkey (key, master) |
|-----|---------------------------|--------------------------|
| 1 | GND (+ actuation return) | GND |
| 2 | **VCC ← powers the lock** (VSYS in) | **VSYS** (battery/system rail out) |
| 3 | `SDA` ↔ PB1 | `LOCK_SDA` (PA6, I2C3) |
| 4 | `SCL` → PB0 (clock + wake) | `LOCK_SCL` (PA7, I2C3) |

The lock has **no local battery** — its VCC (and the boost/actuator draw) comes in
on J2.2 from ephemerkey's VSYS rail. **Current caveat:** a 12 V solenoid pull-in is
~3–4 A from VSYS, beyond a JST-PH contact (~2 A) and ephemerkey's load-share path —
favor the 6 V servo / low-duty buffered by C5/C8, or run a heavier dedicated feed.
The I2C pull-ups live on ephemerkey at +3V3 (do not pull the bus to VSYS — the STM32
pins are 3.3 V-domain). The lock (running at VSYS) reads the 3.3 V idle
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
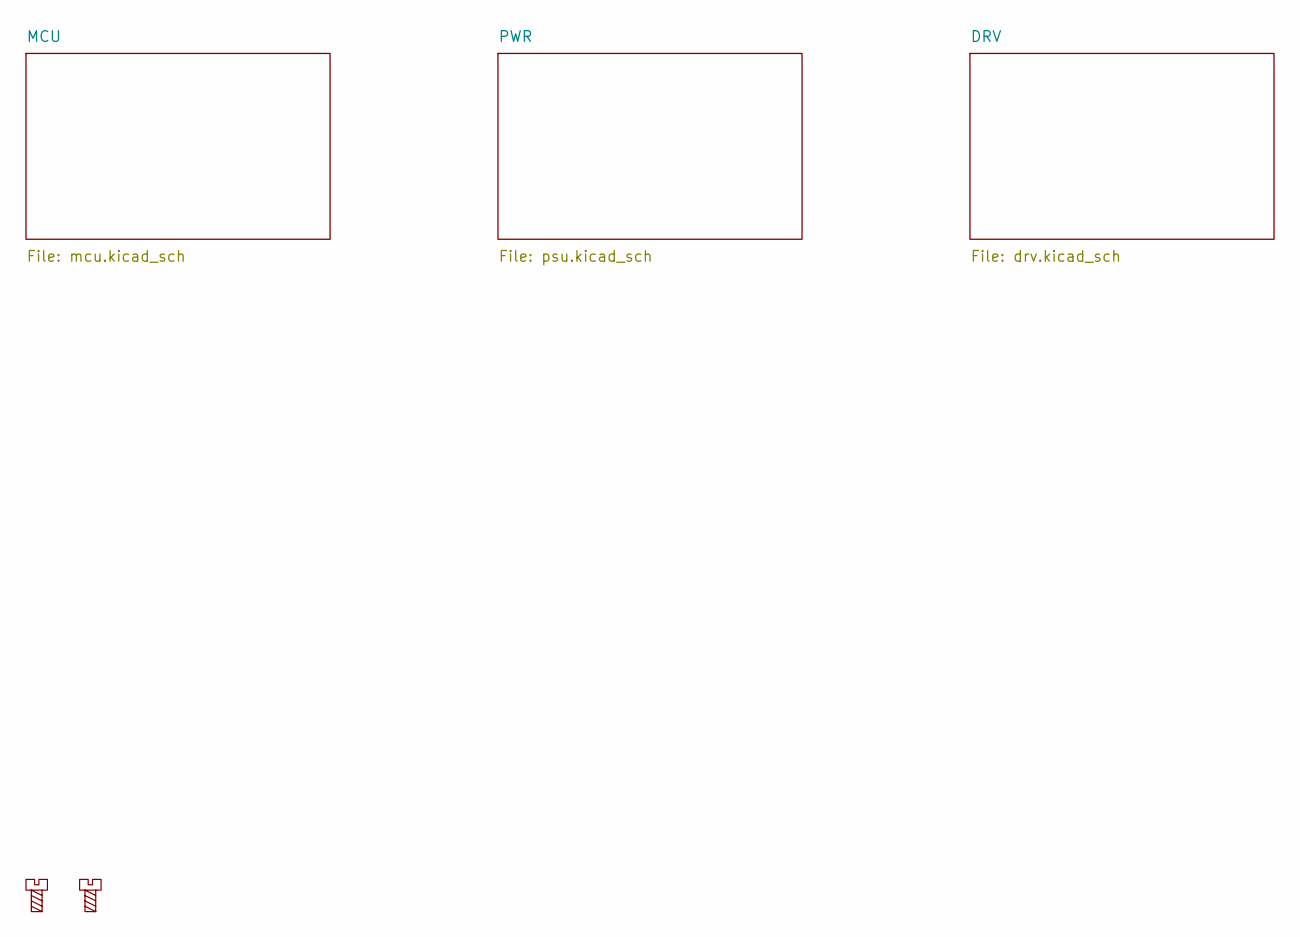
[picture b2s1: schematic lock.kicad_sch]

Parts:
H2, H3: MountingScrew; MountingHole_3.2mm_M3_Pad_TopBottom

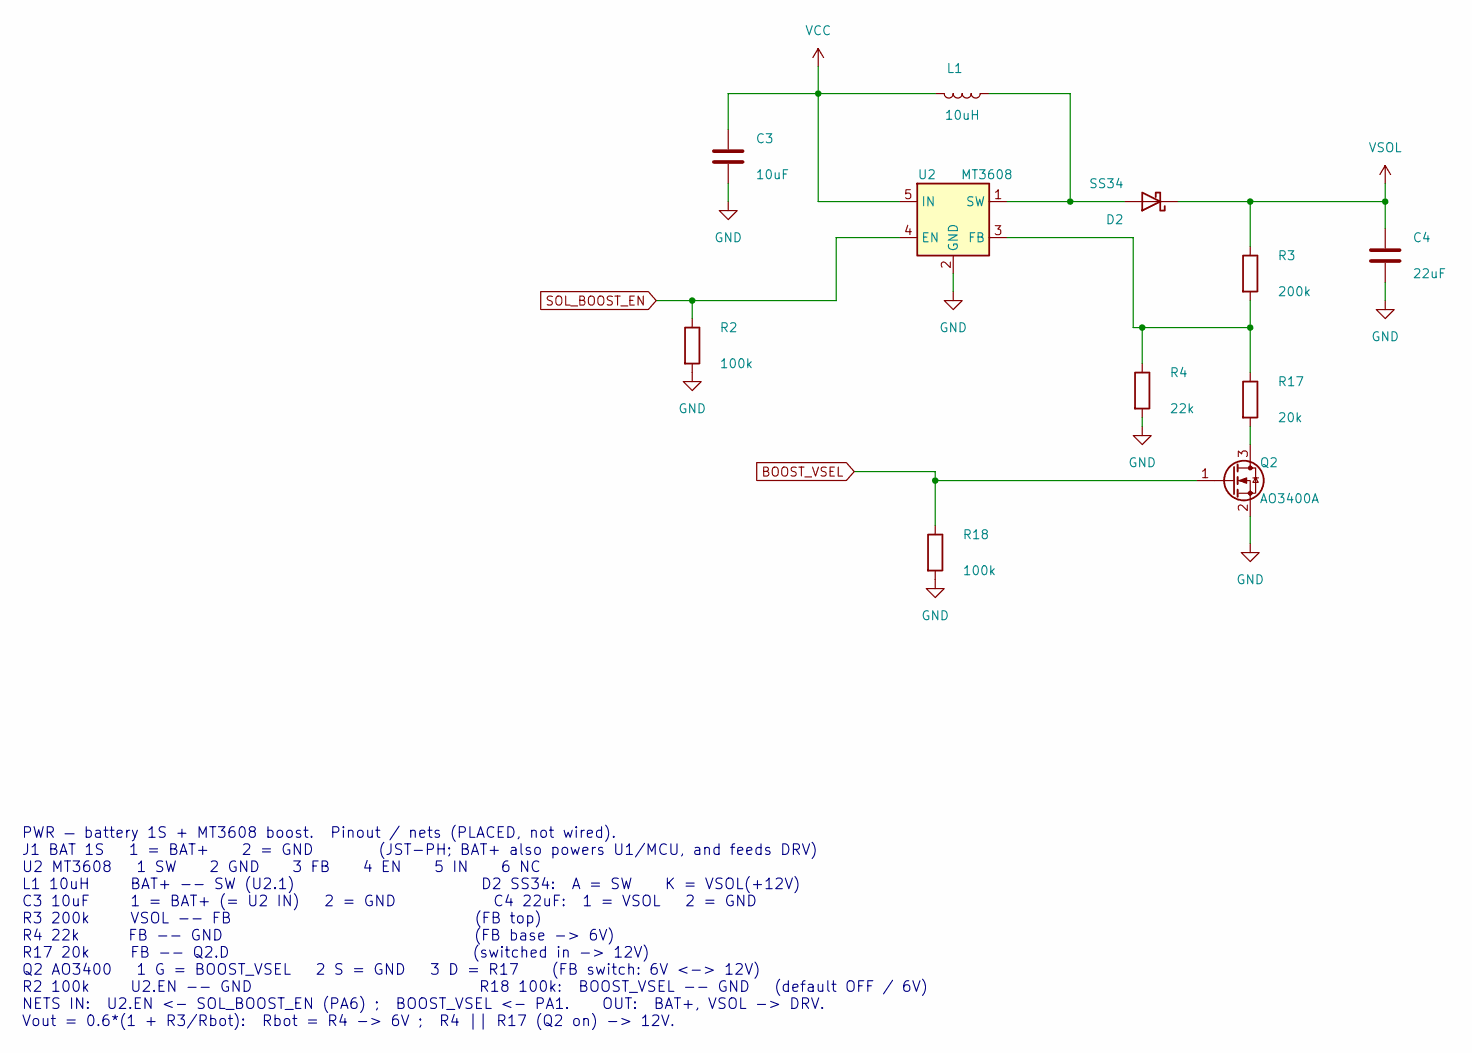
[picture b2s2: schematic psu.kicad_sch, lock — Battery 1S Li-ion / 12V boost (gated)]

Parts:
C3: 10uF; C_0805_2012Metric; LCSC C15850
C4: 22uF; C_1206_3216Metric; LCSC C12891
D2: SS34; D_SMA; MPN SS34; LCSC C8678
L1: 10uH; L_Changjiang_FNR6045S; MPN FNR6045S100MT; LCSC C168076
Q2: AO3400A; SOT-23; MPN AO3400A; LCSC C20917
R2, R18: 100k; R_0402_1005Metric; LCSC C25741
R3: 200k; R_0402_1005Metric; LCSC C25764
R4: 22k; R_0402_1005Metric; LCSC C25768
R17: 20k; R_0402_1005Metric; LCSC C25765
U2: MT3608; SOT-23-6; MPN MT3608; LCSC C84817

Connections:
BOOST_VSEL: Q2.1 (G), R18.1; also elsewhere on the board
GND: C3.2, C4.2, Q2.2 (S), R2.2, R4.2, R18.2, U2.2 (GND); also elsewhere on the board
unnamed: D2.2 (A), L1.1, U2.1 (SW)
unnamed: Q2.3 (D), R17.2
unnamed: R3.2, R4.1, R17.1, U2.3 (FB)
SOL_BOOST_EN: R2.1, U2.4 (EN); also elsewhere on the board
VCC: C3.1, L1.2, U2.5 (IN); also elsewhere on the board
VSOL: C4.1, D2.1 (K), R3.1; also elsewhere on the board

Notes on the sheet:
PWR — battery 1S + MT3608 boost. Pinout / nets (PLACED, not wired). J1 BAT 1S 1 = BAT+ 2 = GND (JST-PH; BAT+ also powers U1/MCU, and feeds DRV) U2 MT3608 1 SW 2 GND 3 FB 4 EN 5 IN 6 NC L1 10uH BAT+ -- SW (U2.1) D2 SS34: A = SW K = VSOL(+12V) C3 10uF 1 = BAT+ (= U2 IN) 2 = GND C4 22uF: 1 = VSOL 2 = 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

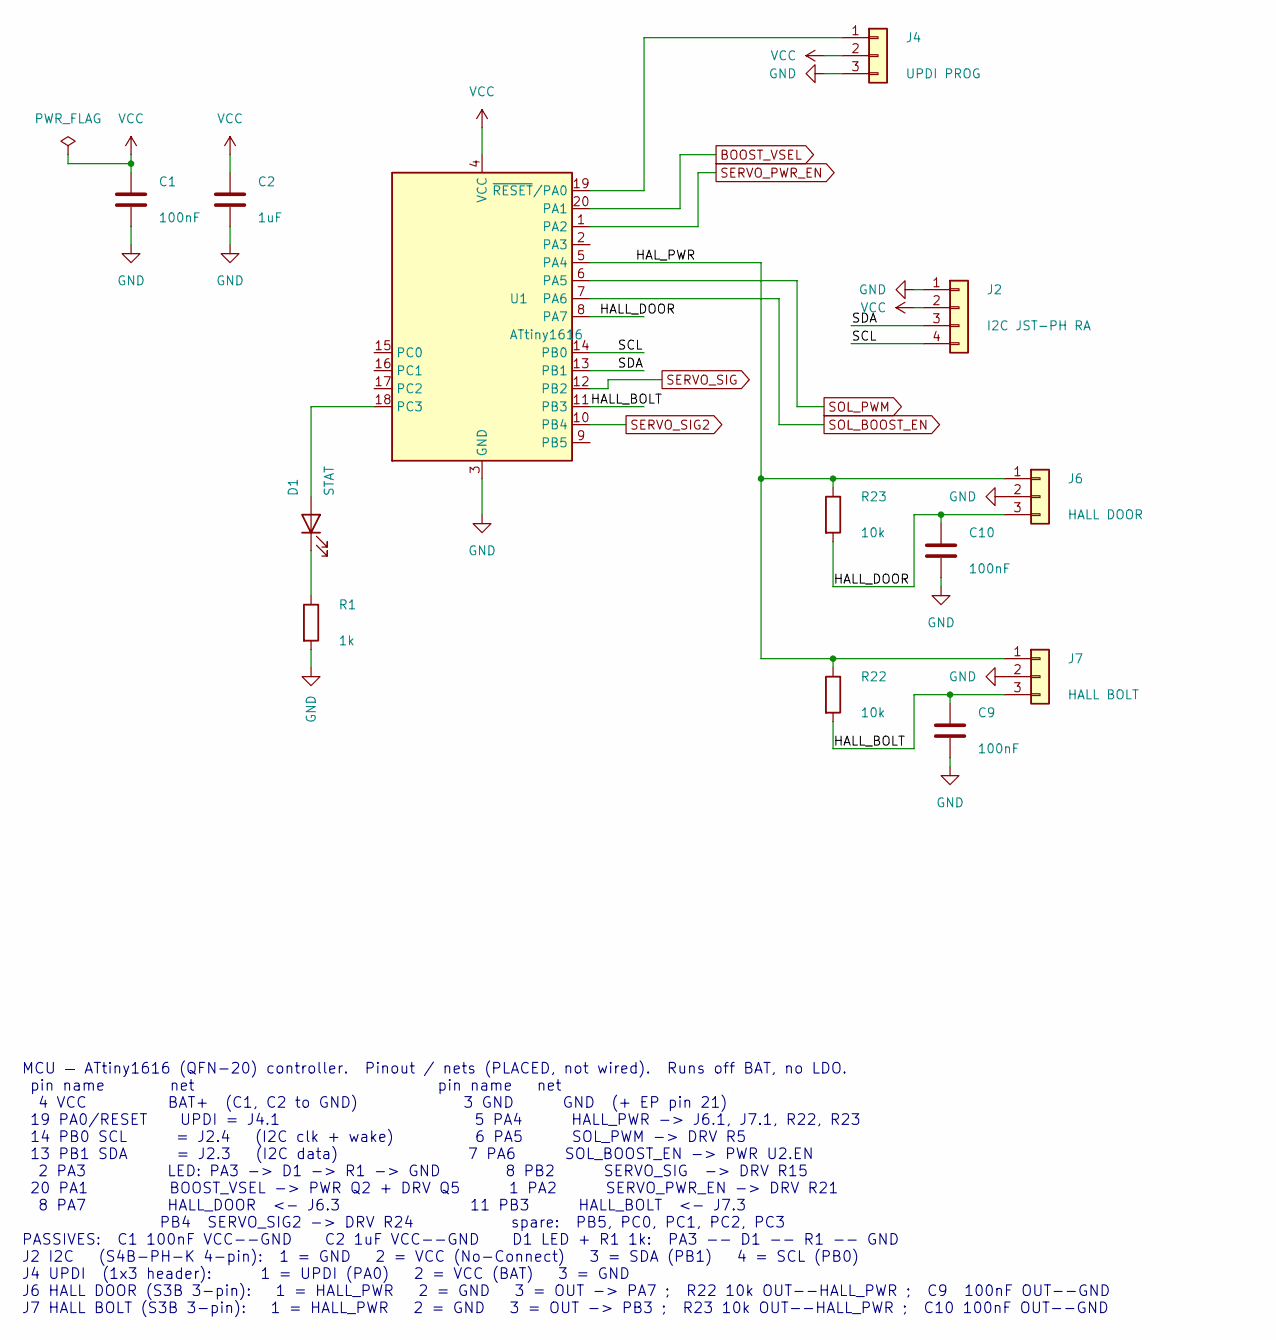
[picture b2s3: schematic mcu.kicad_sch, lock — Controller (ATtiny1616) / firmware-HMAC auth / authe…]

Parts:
C1, C9, C10: 100nF; C_0402_1005Metric; LCSC C1525
C2: 1uF; C_0402_1005Metric; LCSC C29266
D1: STAT; LED_0402_1005Metric; MPN LTST-C281KGKT; LCSC C160479
J2: I2C JST-PH RA; JST_PH_S4B-PH-K_1x04_P2.00mm_Horizontal; MPN S4B-PH-K-S; LCSC C157926
J4: UPDI PROG; PinHeader_1x03_P2.54mm_Vertical
J6: HALL DOOR; JST_PH_S3B-PH-K_1x03_P2.00mm_Horizontal; MPN S3B-PH-K-S; LCSC C157929
J7: HALL BOLT; JST_PH_S3B-PH-K_1x03_P2.00mm_Horizontal; MPN S3B-PH-K-S; LCSC C157929
R1: 1k; R_0402_1005Metric; LCSC C11702
R22, R23: 10k; R_0402_1005Metric; LCSC C25744
U1: ATtiny1616; VQFN-20-1EP_3x3mm_P0.4mm_EP1.7x1.7mm; MPN ATTINY1616-MNR; LCSC C507118

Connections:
/MCU/HALL_BOLT: C9.1, J7.3, R22.2, U1.11 (PB3)
/MCU/HALL_DOOR: C10.1, J6.3, R23.2, U1.8 (PA7)
/MCU/HAL_PWR: J6.1, J7.1, R22.1, R23.1, U1.5 (PA4)
/MCU/SCL: J2.4, U1.14 (PB0)
/MCU/SDA: J2.3, U1.13 (PB1)
BOOST_VSEL: U1.20 (PA1); also elsewhere on the board
GND: C1.2, C2.2, C9.2, C10.2, J2.1, J4.3, J6.2, J7.2, R1.2, U1.3 (GND), U1.21 (GND); also elsewhere on the board
unnamed: D1.2 (A), U1.18 (PC3)
unnamed: D1.1 (K), R1.1
unnamed: J4.1, U1.19 (~RESET/PA0)
SERVO_PWR_EN: U1.1 (PA2); also elsewhere on the board
SERVO_SIG: U1.12 (PB2); also elsewhere on the board
SERVO_SIG2: U1.10 (PB4); also elsewhere on the board
SOL_BOOST_EN: U1.7 (PA6); also elsewhere on the board
SOL_PWM: U1.6 (PA5); also elsewhere on the board
VCC: C1.1, C2.1, J2.2, J4.2, U1.4 (VCC); also elsewhere on the board

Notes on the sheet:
MCU — ATtiny1616 (QFN-20) controller. Pinout / nets (PLACED, not wired). Runs off BAT, no LDO. pin name net pin name net 4 VCC BAT+ (C1, C2 to GND) 3 GND GND (+ EP pin 21) 19 PA0/RESET UPDI = J4.1 5 PA4 HALL_PWR -> J6.1, J7.1, R22, R23 14 PB0 SCL = J2.4 (I2C clk + wake) 6 PA5 SOL_PWM -> DRV R5 13 P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
